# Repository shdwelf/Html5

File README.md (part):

# bip39-haiku-workbench

Offline workbench for mining **BIP-39 mnemonics that scan as 5-7-5 haiku**, deriving
their BIP-44 addresses, and moving data between tools through a **piped inbox**.

The application now combines both repository lineages. The canonical main canvas is
the complete uploaded **23 August Gen2 Webxdc/quine build**, with a surgical Poetry
validator repair applied before it executes rather than replacement look-alike
components. The small `⌘` switcher opens the maintained TypeScript recovery suite
and every other distinct, non-empty HTML application from the gen-2 patch.

```bash
npm install
npm run dev     # http://localhost:5173
npm test        # full test suite, including byte-identity locks for the uploads
npm run build   # dist/index.html + dist/bip39-haiku-workbench.xdc
```

The production build is inlined by `vite-plugin-singlefile`, so `dist/index.html`
runs standalone from the filesystem. `scripts/build-xdc.mjs` then packages that
same combined application, its icon, manifest, and static companion tools as a
Webxdc ZIP for ArcaneChat / Delta Chat.

## Combined codebases

| Switcher entry | Source | Integration rule |
| --- | --- | --- |
| **Gen2 · Aug 23** (default) | `bip39-haiku-workbench-gen2-2026-08-23T11-46-10-756Z.html` | Full uploaded 12-tool canvas plus strict Poetry syllable repair |
| **Gen2 · Aug 14** | `bip39-haiku-workbench-gen2-2026-08-14T20-01-22-058Z.html` | Exact earlier seven-tool generation |
| **Quip build** | `bip39-haiku-workbench-quip.html` | Exact mnemonic explorer bundle |
| **Classic wallet** | `bip39_haiku_wallet.html` | Exact standalone miner and encrypted wallet list |
| **Pattern validator** | `haikubip39.html` | Exact classic haiku/repeated-word validator |
| **Recovery suite** | `src/` | Maintained React/TypeScript tools described below |

The applications run in same-origin `iframe srcdoc` boundaries because every upload
is already a complete compiled document with its own React runtime, global CSS,
`#root`, storage, and download handlers. This is deliberate isolation, not a visual
port: `test/codebase-archive.test.tsx` pins the original SHA-256 of all five documents,
and `test/poetry-validation.test.ts` signature-locks the two targeted Gen2 repairs.
The old Poetry counter double-subtracted consonant-`le` endings, while its line builder
could abandon a target after drawing a word that did not fit. The repair shares the
validator pronunciation table, only selects words that fit the remainder, and accepts
exact form counts—never a third line of 4 or 6 for 5-7-5. The second 23 August upload
is omitted only because it has the same SHA-256 as the first; `bip39haiku.html` is
omitted because it is zero bytes.

## Provenance

This repository was empty apart from a README. The application source was recovered
from the archive repo [`shdwelf/Html5-sync-incoming`](https://github.com/shdwelf/Html5-sync-incoming):

| Piece | Recovered from |
| --- | --- |
| Workbench app (React + Vite + Tailwind, `src/lib/wallet.ts`, `src/lib/syllables.ts`, `src/lib/enso.ts`) | `build-bip-39-haiku-wallet.zip` |
| Piped inbox concept and UI | `hyper-portal-2.27.0-PIPED-installer.html` (inside `Internal storage.7z`) |
| Recovery Lab (missing-word brute force, typo/anagram repair, vanity mining) | `crypto-mnemonic-mining-app.zip` |
| Art Gallery catalog, greedy 5-7-5 fallback, syllable-exception cleanup | vanilla workbench in [`shdwelf/Html5`](https://github.com/shdwelf/Html5) (`js/haiku-catalog.js`, `js/syllables.js`) |
| Vault file format + standalone decryptor | `HAIKUv4/v5`/`DECRYPTORv1.html` lineage (`Haiku Supplies.zip`) and the vanilla workbench's WebCrypto vault |

The two never shipped together: the haiku workbench had no inbox, and the
hyper-portal build that had the inbox had no haiku tool. Wiring them together —
and repairing the inbox on the way — is what this repo does.

`scripts/wormhole-fetch.mjs` is a small utility kept from that recovery work:
given `WH_URL=<link>` it opens a wormhole.app drop in real chromium (via
playwright) and captures every file — the link is end-to-end encrypted in the
URL fragment, so only a real browser can decrypt it. It runs anywhere
playwright + chromium are installed (a laptop, a GitHub runner with the
workflow permission).

## Repository-wide Java / TiddlyWiki editions

The new [Repository Wiki build](tools/wiki-workspace/README.md) produces actual
ACME/TJWS-hosted `wiki.in.a.jar`, `more.wiki.in.a.jar`, and `tiddlywiki.in.a.jar`,
plus a native TiddlyWiki HTML/Webxdc edition and MediaWiki XML export. Each JAR
contains a per-file source catalog and a deduplicated exact-byte repository vault,
with private caches/credential paths explicitly excluded. The extended library
adds backlinks, bibliographic URLs, revision conflicts/history and Haiku-v1
compatible encrypted page/file exchange. These are **new repository editions**,
not a claim to have recovered historical More Wiki 0.9.9 or translated arbitrary
JavaScript into JavaCard. See the [source-checked research and limitations](docs/wiki-workspace-research-2026-10-15.md).

```sh
npm ci
npm run build:wiki-workspace           # JDK 11+, Python 3, tar, curl; outputs dist/wiki/
java -jar dist/wiki/more.wiki.in.a.jar 3003
npm run test:wiki-workspace
npm run test:wiki-server               # real executable-JAR HTTP + persistence tests
```

The classic wiki's Calendar now uses font-independent SVG navigation, an
always-visible month grid and an event-page form; no pre-existing events are
required. TiddlyWiki HTML/XDC carry previews and metadata; the complete eligible
binary vault lives in the JAR editions. Nothing is uploaded to a remote wiki.

## Standalone viewers

- **[HTML5 Offline Viewer](offline-viewer.html)** — curated public catalogue for the locally bundled Helios Observatory and Prime Viewer apps, plus the local WebXDC player. `python3 scripts/build-private-html5-offline-viewer.py` creates a separate ignored delivery ZIP from the same fixed app allowlist.
- **[HTML5 Offline Library for Android](apps/html5-offline-launcher/README.md)** — public and curated private APK build instructions. CI publishes only the public APK artifact; the two-app private APK is built and verified without public artifact upload.
- **[Wiki in a Jar](wikiinajar.html)** — the 2008 USB-stick personal wiki (`wiki.in.a.jar` 0.8) rebuilt as one offline HTML file and a Webxdc bundle: same `.wiki` page model, same `[[wiki:]]`/`[[img:]]`/`[[djvu:]]`/`[[tags:]]` namespaces, vCard contacts, DjVu reading via the vendored WASM decoder, and webxdc chat sync. Ships as `wikiinajar.xdc` (`npm run build:wikiinajar`) with the repository Markdown library (root deep dives + `docs/*.md`) converted to wiki pages in its Docs tab; see [the deep dive](wikiinajar-deep-dive.md), the seeded **Wiki in a Jar** documentation page inside the app, and the Java-side patch in [tools/wikiinajar/](tools/wikiinajar/).
- **[Keyspace Viewer](keyspace.html)** — BIP-39 geometry, measured statistical layers, wallet derivatives, and keyspace projections.
- **[Prime Viewer](prime.html)** — exact prime atlas, residue-class solar system, prime constellations, counting statistics, gaps, and integer inspection. See [PRIME.md](PRIME.md).
- **[Helios Observatory](astronomy.html)** — time-propagated solar orrery, curated celestial catalog, Earth-centered NEO radar, and modeled meteor streams. See [ASTRONOMY.md](ASTRONOMY.md).
- **[Flash Decompiler Timeline](flash-decompiler.html)** — Wayback/NATA2-style raw SWF retrieval, configurable CORS proxy triage, Behind The Dune version timeline, easter-egg notes, and a GitHub Actions path for JPEXS/FFDec decompilation without committing large NSFW binaries.
- **[Red October · 4D Command Theater](public/apps/red-october-command-viewer/)** — an offline story-index globe, selectable schematic silhouettes, story/time controls, VRML 2.0 and Xena XML export. The map markers are fictionalized narrative anchors, not real track data; the hull model has no precise internal layout. Ships as `red-october-command-viewer.xdc`; see [the viewer source/provenance research](docs/red-october-4dwm-research-2026-10-09.md) and [the Archive.org/Jane’s/Bulletin source audit](apps/red-october-command-viewer/data-sources/archive-research.md).
- **[Greeran Family Tree · 4DWM](greeran-family-4dwm.html)** — the Drive family-tree Webxdc with an offline spinning globe, playable 1774–2023 record timeline, Tree-of-Life preface, baseline GEDCOM export, and public-domain World English Bible EPUB. The first-name merge remains pending until an authorized Kirkpatrick ARJ and raw GEDCOM are available. See [the import/build notes](docs/greeran-family-4dwm.md) and [the ebook/data status](docs/greeran-family-tree-ebook-and-data-status.md).
- **[FOUR CORNERS 4Dwm](four-corners.html)** — the only place four US states meet: the surveyed quadripoint, Navajo volcanic field necks, the San Juan energy basin, the uranium legacy, and the ancestral Puebloan core, over a curated IDW relief that is honest about not being a DEM. See [docs/four-corners.md](docs/four-corners.md). Ships as `four-corners.xdc` and as the [TI calculator port](#four-corners-on-ti-calculators-four-corners-calc) below.
- **[SoCal Subsurface 4Dwm](socal-subsurface.html)** — an offline basin theater with terrain, geocache GPX import, radio/propagation and orbital views. Ships as `socal-subsurface.xdc`, plus the single-file [`socal-subsurface-inlined.html`](socal-subsurface-inlined.html) / `socal-subsurface-inlined.xdc` edition; the legacy download name `planet-viewer-4dwm.xdc` now carries this same canonical SoCal package and manifest.
- **[Greeran Subsurface 4Dwm](greeran-subsurface.html)** — the Greeran book's 2001 biography deep-dive (Glendora → West Covina → Goleta → Santa Barbara) rendered as a SOCAL-style subsurface theater. Ships as `greeran-subsurface.xdc`.
- **[Glendora High 4Dwm](glendora-high-4dwm.html)** — Class of 2001 at 1600 E Foothill Blvd, "now that I am a graduate". Ships as `glendora-high-4dwm.xdc`.
- **[ESGVROP 4Dwm](esgvrop-4dwm.html)** — East San Gabriel Valley ROP & Technical Center, the summer-2001 deep dive across the Del Norte and Sunflower campuses. Ships as `esgvrop-4dwm.xdc`.
- **[Dalton Race 4Dwm](dalton-race-4dwm.html)** — Big Dalton / Little Dalton terrain with pips, route pointers, and VRML export. Ships as `dalton-race-4dwm.xdc`.
- **[INGRESS INTEL 4Dwm](ingress-intel.html)** — an Ingress intel theater that actually tries to connect: a six-rung connection ladder (same-origin → your relay → public CORS proxy → pasted capture → webxdc peer → offline register) with a verdict and a fix printed per rung, the same intel payload drawn on a planet globe with geodesic links, spherical control fields and a live day/night terminator *and* on the SoCal basin plate, and an honest `SIM` watermark whenever nothing live answered. Decodes/encodes `getEntities`, portal-detail and plext payloads, IITC GeoJSON/KML/CSV exports and intel permalinks. Ships as `ingress-intel.xdc`. See [docs/ingress-intel-map-viewer.md](docs/ingress-intel-map-viewer.md) and the [connector research](docs/ingress-intel-connector-research-2026-10-07.md).
- **[CASEFILES · 4DWM](casefiles.html)** — the static-analysis lab for the 1998 kr0me corp Tripod library and the 1996 Rodger Ramrod DOS4GW package: Wayback CDX recovery behind a SHA-1 gate, fflate unzip in memory, SLEIGH x86 16/32, the Ghidra decompiler as WebAssembly — and a 4DWM plate that draws the capture corpus as a ridged relief over a playable capture-date timeline, and whatever artifact is on the table as a bit-plane relief with an offset sweep. Motif-style pips carry the record; VRML 2.0 exports the current field. Ships as `casefiles.xdc` (a real webxdc ZIP) and as the single-file `casefiles-inlined.html`; see [docs/casefiles-4dwm.md](docs/casefiles-4dwm.md).
- **[Lantronix Lab](lantronix-lab.html)** — the deep dive that starts at a thumb-sized Lantronix xPort Pro (16 MB flash, ColdFire, µClinux) and ends at a generated EAGLE design for a mains-powered RS-232 ↔ RJ45 wallplug: a device matrix that keeps DSTni-EX (x86) and DSTni-FX (ColdFire) apart, a client-side firmware triage tool that goes magic → container → architecture → Ghidra language, the µClinux stack Lantronix actually ships with a DistroWatch-reality-check on alternatives, a JVM-vs-Java-Card panel with a real `.class`/`.cap` reader and bytecode disassembler, and an EDA viewer that renders the generated `.sch`/`.brd` and re-runs the design rules in the browser. See [docs/lantronix-uclinux-deep-dive-2026-10-08.md](docs/lantronix-uclinux-deep-dive-2026-10-08.md) and [hardware/lantronix-wallplug/](hardware/lantronix-wallplug/).
- **Wallplug family** — the xPort Pro wallplug is now one of four generated, rule-checked EAGLE designs built by a single design-agnostic pipeline: a **WiMAX CPE** carrier for a PCI Express Mini Card 802.16e modem (Intel Centrino 6250; USB half wired, PCIe half honestly left open), a **Raspberry Pi Zero 2 W wall-socket** carrier with wired Ethernet (WIZnet WIZ850io on SPI0) and Ethernet-over-powerline (chargebyte PLC Stamp mini 2 on SPI1), and a standalone **HomePlug Green PHY ↔ Ethernet bridge** (QCA7005 + ESP32 + W5500). Every pad coordinate is imported from a published KiCad footprint by `tools/import-kicad-footprints.mjs`; creepage follows the chargebyte datasheet's 8 mm / 6.5 mm / 4000 Vac figures where that module is fitted; and `tools/replacement-parts.mjs` records 83 sourced substitutes with verdicts, including the ones marked *not-a-substitute*. See [docs/wimax-pi-powerline-variants-2026-10-08.md](docs/wimax-pi-powerline-variants-2026-10-08.md) and [hardware/](hardware/).
- **[CITY SUBSURFACE 4Dwm](lawrence-subsurface.html)** — the shared SoCal-family city engine ships as fifty-nine apps: Lawrence KS, Atlanta GA, Kansas City MO, Buffalo NY, Toronto ON, statewide California/Nevada/Arizona/Utah/Colorado/New Mexico/Oregon/Washington/Idaho/Montana/Wyoming/North Dakota/South Dakota/Nebraska/Kansas/Oklahoma/Texas/Iowa/Missouri/Minnesota/Louisiana/Mississippi/Alabama/Georgia/Wisconsin/Michigan/Illinois/Indiana/Ohio/Pennsylvania/Arkansas/Kentucky/Tennessee/Virginia/West Virginia/North Carolina/South Carolina/Florida/Maryland/Delaware/New Hampshire/Vermont/Maine/Massachusetts/Connecticut/Rhode Island/Alaska/New Jersey/New York/Hawaii frames, and Guam, American Samoa (Tutuila–Manuʻa), U.S. Virgin Islands and Midway territory frames. Each keeps the Gazetteer, local `rec.geocache` GPX import, BagIt export and plan view. Lawrence has a disclosed 8×8 USGS 3DEP sample grid plus five verified GNIS points; the state/territory starter registers use per-ID GNIS primary points with synthetic relief rather than claiming DEMs. Build with `npm run build:city-subsurface`; see [the evidence/build notes](docs/city-subsurface.md).
- **[COUNTRY VIEWER](country-viewer.html)** — the PC-Globe-style country viewer (S4 country thread): an offline, searchable full-coverage register of 233 countries/territories with CIA World Factbook notes, packaged as `country-viewer.xdc` — capital and reference-point coordinates, area, population, languages, government type, and national-anthem titles — pinned to `factbook/factbook.json@144d6977b2b0` with per-file SHA-256 in `resources/country-viewer/`. Build the dataset and bundle with `npm run build:country-viewer`. The 1990 PC Globe database itself is decoded by the dependency-free Java reader in `tools/pcglobe/` (dump in `research/pcglobe-java/`), and the [planet viewer](planet-viewer-4dwm.html) opens on a GLOBE plate that reuses the Red October globe with these capitals as markers.
- **[Historical Network Viewer — Keyhole slice](historical-network-viewer.html)** — the S6 evidence viewer for Denver's Keyhole BBS: dated observations, snapshot rights/capture status, a city-level place with no invented pin, merge/rejected-match logs, negative FidoNet searches, JSON/CSV export, and local TEXTFILES plus FTS-5000 FidoNet nodelist import with browser-side SHA-256. It is a citation fixture and local-import tool, not a bundled historical dataset; see [the fixture notes](docs/historical-network-keyhole-fixture-2026-10-22.md) and [FidoNet adapter notes](docs/historical-network-fidonet-adapter-2026-10-22.md).
- **[FOUR CORNERS · calculator port](four-corners-calc.html)** — the bench for the TI-83/89/92 port: it runs the port's own C core transpiled to an ES module, so the preview *is* the port.

Every 4Dwm-family Webxdc rebuilds from one command — `npm run build:4dwm`
chains the fourteen standalone packagers (casefiles, bluetops, cheyenne,
dalton-race, esgvrop, four-corners, glendora-high, greeran-family,
greeran-subsurface, ingress-intel, sanborn-restaurant, SoCal Subsurface (also
mirrored to the legacy `planet-viewer-4dwm.xdc` filename) and its inlined
edition, vincennes), then
builds the fifty-nine shared city/state/territory bundles; each app also has its own
`npm run build:<name>`, and `npm run check:casefiles` proves CASEFILES' two
derived artifacts still match their sources byte for byte.

## Tools

| Tab | Purpose |
| --- | --- |
| **Ensō Forge** | Parameterised ensō brushstroke; its packed *Ensō ID* doubles as the vault password. |
| **Haiku Wallet** | Mines 128-bit mnemonics until the 12 words partition into 5-7-5, derives `m/44'/0'/0'/0/0`, stores them in an AES-256 vault. |
| **Inspector** | Validates a phrase's BIP-39 checksum, shows its syllable/5-7-5 breakdown, derives address + xpub. |
| **Recovery Lab** | Brute-forces `?` words, repairs typos/anagrams, mines BTC vanity addresses — optionally pinned to an address fragment you know is yours. |
| **Art Gallery** | 100 curated checksum-valid BIP-39 art patterns (repeat stems, haiku/poetic scans), re-verified live on every render. |
| **MonKey Miner** | Mines Banano wallets for rare monKey accessories, fully offline. |
| **Autobiography** | Chapters plus an embedded filesystem; exports as one self-contained HTML book. |
| **Crypto Cookbook** | The 83-section reference, framed byte-identical from `/apps/cookbook/`. |
| Terminal / wAves / Market | Carried over from the original build. |

## Recovery Lab

Ported from the recovered `crypto-mnemonic-mining-app` (June 2026, ethers-based)
onto this repo's own stack — `@scure/bip39` for checksums, the wallet's BTC
P2PKH derivation instead of ethers/bananojs, no new heavy dependencies.

**Find `?` words.** Mark each unread word with `?`. A BIP-39 phrase carries its
own checksum, so of the 2048 words that could fill a slot only ~1 in 16
survives for a 12-word phrase (1 in 256 for 24 words) — the checksum does most
of the work. One missing slot scans instantly; two walks 2048² = 4.2M
combinations chunked and cancellably (a few minutes at most; more than two is
out of scope for a browser lab).

**Repair typos & anagrams.** Words outside the wordlist are replaced by their
anagrams (the wordlist has 56 anagram classes: `canoe/ocean`, `armed/dream`,
`alert/alter/later`…) and near edits — Levenshtein distance ≤ 2. If every word
is valid but the checksum still fails, each single word is tried against its
edit-distance-≤ 1 neighbours plus anagram mates, catching the silent swap that
spell-check cannot see.

**Pinning to an address.** Repairs and fills frequently have *several*
checksum-valid outcomes — the checksum cannot tell them apart. Paste the first
characters of an address you know the wallet owned and only candidates whose
BTC legacy derivation contains that fragment survive. That is also what makes
recovery deterministic instead of "first 20 valid hits".

**Vanity mining.** Mines fresh 12-word mnemonics until the BTC legacy address
starts with your prefix (case-sensitive Base58; the leading `1` is optional).
Each extra character is ~58× the work: two characters are seconds, three are
minutes, four are a long night. Cancels like everything else.

## Art Gallery

The 100-entry catalog shipped with the vanilla workbench port
(`js/haiku-catalog.js` in `shdwelf/Html5`): 40 eleven-word repeat stems with
their checksum word, 20 fifteen-word, 10 twenty-four-word patterns, and 30
haiku/poetic scans. In BIP-39 the last word is never free — its low bits are
the checksum of everything before it — so an eleven-word stem of one repeated
word pins exactly one valid ending. The stem is chosen; the checksum decides
the last word. These are found art.

Every card re-validates its phrase against the real BIP-39 checksum on render
(and `test/catalog.test.ts` locks all 100), so a corrupted import is visible
immediately. Haiku entries display their greedy 5-7-5 layout with per-line
syllable counts, and any entry can be piped to the Inspector.

## Inspector upgrades

- **Per-word chips** under the input — each word with its syllable count,
  red when not in the wordlist (ported from the mining app's live validation).
- **Explorer section** (Coleman-style): BIP-39 passphrase ("25th word"),
  custom derivation path, seed hex, root xpub, and a first-N accounts table.
  Private keys stay hidden behind a per-row reveal; the root xprv is never
  rendered. A passphrase changing every derived address is demonstrated in
  `test/syllables-explorer.test.ts`.
- **Greedy 5-7-5 fallback** now lives in `src/lib/syllables.ts`
  (`greedy575`), shared by the Inspector and by `itemFromMnemonic`, replacing
  the old behaviour of dumping a non-haiku phrase onto a single line. The
  ported version had a defect: words after the third line filled were
  silently dropped. Fixed here — the layout always accounts for every word —
  and locked by test.
- The syllable **exception table** dropped three dead keys (`area51`,
  `create_`, `science_`) that could never match after non-letters are
  stripped.

## Vault files and the standalone decryptor

Besides the existing crypto-js exports, the wallet now speaks a
format-designed-for-archival vault file:

```
haiku-vault-v1.<base64( 0x01 | salt(16) | iv(12) | ciphertext‖tag )>
```

AES-256-GCM, PBKDF2-HMAC-SHA256 × 120,000, salt separate from the IV so one
Ensō ID can safely back multiple files. Implemented with `@noble/ciphers` in
the app; round-trip, wrong-password and single-character-tamper cases are
covered by `test/vaultfile.test.ts`.

**🧰 Standalone decryptor ⬇** generates a single self-contained HTML page
(no imports, no network, verified by test) that decrypts `.haikuvault` files
with native WebCrypto — optionally with the current vault pre-embedded. Save
it next to your backups: it opens from a USB stick in fifty years' time, which
is the whole point of an offline vault. **📥 Import .haikuvault** decrypts
with the current Ensō ID and merges without duplicates.

## The piped inbox

Any tool can **park** a value in the inbox (`📤 Pipe`) or **pull** one out
(`📥 Pull from Pipe`). The floating inbox can also **push** a value straight into
a tool, which focuses that tab and delivers the payload.

Content is typed (`mnemonic`, `haiku`, `address`, `xpub`, `json`, `text`) and the
UI only offers targets that accept the type — so a mnemonic mined in the wallet
can be sent to the Inspector, but an address cannot.

### What was broken

The original provider (`hyper-portal-2.27.0-PIPED-installer.html`) kept a single
`inboundPayload` slot and no persistence. Four concrete defects, each now covered
by a regression test in `src/pipe/PipeProvider.test.tsx`:

1. **Back-to-back sends lost data.** Delivery was one `useState` slot, so
   `sendToTool(a); sendToTool(b)` overwrote `a` before any consumer ran — only
   `b` arrived. Deliveries are now an append-only queue drained per tool.

2. **The inbox did not survive a reload.** Pipes lived only in React state, which
   makes "park this for later" meaningless across a refresh. Pipes and in-flight
   deliveries now persist to `localStorage`, with corrupt/quota-limited storage
   degrading to memory instead of throwing.

3. **Empty content read back as a miss.** `consumePipe` ended in
   `?.content || null`, so an empty string — legitimate payload — was
   indistinguishable from a missing pipe. Now `?? null`.

4. **Colliding ids.** Ids came from `Math.random().toString(36).substring(2,10)`.
   Since rows are keyed by id and `removePipe` filters on it, a collision deletes
   the wrong entry. Now `crypto.randomUUID()` with a timestamped fallback.

Additionally, consumption used to be an impure read (`consumeInbound` returned the
payload *and* cleared it), which is fragile under React StrictMode's double-invoked
effects. Delivery is now explicit: `usePipeReceiver` hands the payload to a handler,
records the delivery id in a ref, and acks it — so a repeated effect run cannot
apply the same payload twice.

I verified 1, 3 and 4 by running the new tests against a faithful replica of the
original provider and watching them fail. Defect 2 is likewise reproduced. The
late-mount guarantee (a delivery waits for a tool that has not been opened yet) is
hardening rather than a reproduced regression — the old code happened to survive
that case.

### Using it in a tool

```tsx
// produce
<PipeOutButton draft={{
  content: item.mnemonic, contentType: "mnemonic",
  sourceId: "wallet", sourceName: "Haiku Wallet", label: `${item.id} mnemonic`,
}} />

// consume: pushed deliveries
usePipeReceiver("inspector", (delivery) => setText(delivery.content));

// consume: user-initiated pull
<PipeInButton accepts={["mnemonic", "text"]} onReceive={(content) => setText(content)} />
```

## Recovered HTML5 apps (`/apps/`)

`npm run dev` also serves the other apps recovered from `Html5-sync-incoming`,
over the dev server's origin rather than `file://`:

| URL | App |
| --- | --- |
| `/apps/` | Index, with a live secure-context / microphone check |
| `/apps/anc-studio/` | ANC Studio Ultra — adaptive multi-band FxLMS over AudioWorklet |
| `/apps/cyberchef/` | CyberChef Renovated Kitchen — 519 recipes after unioning the Html5 and Html5-sync-incoming recipe sets, plus file input and save. Includes QR/Aztec generation and image decoding, CueCat and postal barcode recipes, Avery LabelPro-style N-up labels, an educational multiplicative ElGamal demonstration (not FHE), and offline SFX support. See the [barcode notes](docs/cyberchef-aztec-cuecat.md), [SFX coverage audit](docs/cyberchef-sfx-coverage-audit-2026-10-13.md), [field-cipher deep dive](docs/field-cipher-deep-dive-2026-10-14.md), and [recipe-sourcing notes](docs/recipe-sourcing-round-4-2026-10-14.md) and [round 5](docs/recipe-sourcing-round-5-2026-10-14.md) for the tested cryptography and historical recipes. |
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
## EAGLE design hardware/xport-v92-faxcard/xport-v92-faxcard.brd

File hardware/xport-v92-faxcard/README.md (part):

# xPort Pro V.92 Fax Card — telnet BBS + Group 3 fax in an HP EIO slot

Generated CAD. Do not edit these files: they are emitted by
`tools/build-wallplug-eagle.mjs --design=xport-v92-faxcard` from
`tools/xport-v92-faxcard-model.mjs`, and `--check` re-derives them and compares.

| file | what it is |
| --- | --- |
| `xport-v92-faxcard.lbr` | 18 packages, 15 symbols, 18 devicesets |
| `xport-v92-faxcard.sch` | 1 sheet, 27 instances, 23 nets |
| `xport-v92-faxcard.brd` | 150 × 100 mm, 2 layers, 32 elements, 115 pads — **unrouted on purpose** |
| `BOM.md` | every reference, its package, fit/DNP, zone and note |

## What it does

A card in the HP Enhanced I/O (EIO) expansion-slot form factor that puts a
Lantronix xPort Pro device server and a V.92 56k data/fax modem inside a
printer, bridged by an STM32 Nucleo-64:

```
PSTN ── RJ11 (J3) ── V.92 modem (U3) ── USART1 ── Nucleo-64 (J2) ── USART2 ── xPort Pro (X1) ── RJ45 ── Ethernet
        tip/ring      DAA + Class 1     PA9/PA10                   PA2/PA3                  telnet BBS
```

The xPort Pro's RJ45 and the modem's RJ11 both come out on the EIO faceplate.
The xPort Pro runs the telnet BBS front end; the modem answers and sends Group 3
fax; the Nucleo bridges the two serial links and drives the T.30 session.

## The EIO constraint, and what it forced

EIO uses the **3.3 V signalling of the conventional PCI bus**, will not accept
LIO cards, and is not mechanically interchangeable with MIO. Two consequences:

* **An STM32 cannot enumerate as a PCI target.** Reaching the printer's
  formatter through the slot needs a PCI-to-local-bus bridge. This revision does
  not have one.
* **HP does not publish the EIO pinout.** No finger is energised on a guess.

So `J5` is a 68 × 12 mm **mechanical keep-out carrying no copper**, and the card
takes power from `J1`, a 12 V tap. The card uses the slot for mounting and
faceplate registration and is otherwise electrically independent of the printer.
When the pinout is traced from a donor JetDirect card, `J5` becomes a real
PCI-32 3.3 V finger pattern.

**A Nucleo cannot physically live in the slot** — it is 70 × 70 mm with 8.5 mm of
header above the board. This is a development carrier; a production revision
would put the same MCU down as a bare LQFP.

## Host wiring

| Nucleo-64 | MCU | other side | note |
| --- | --- | --- | --- |
| D1 | PA2 | X1 pin 5 `DIN` | USART2_TX → xPort Pro, via R8 100 Ω |
| D0 | PA3 | X1 pin 4 `DOUT` | USART2_RX ← xPort Pro, via R7 100 Ω |
| D8 | PA9 | U3 `RXD` | USART1_TX → modem, via R4 100 Ω |
| D2 | PA10 | U3 `TXD` | USART1_RX ← modem, via R3 100 Ω |
| D9 | PC7 | U3 `!DCD` | carrier detect |
| D10 | PB6 | U3 `!DTR` | |
| D11 | PA7 | U3 `!RI` | ring indicator |
| VIN | — | 12 V | UM1724 specifies 7–12 V |

**The trap:** on a Nucleo-64, PA2/PA3 are also the ST-LINK virtual COM port
(MB1136 SB62/SB63 ON, SB13/SB14 OFF). Leave the bridges closed and you get a
free USB console, but the ST-LINK shares the xPort Pro link. Open SB62/SB63 for
a production card, or swap the two links.

Both links are 3.3 V TTL end to end — the xPort Pro serial channel and the modem
module are both 3.3 V parts — so there is **no level shifter**. The 100 Ω
resistors are hot-plug and fault limiting, not translation.

No hardware flow control: 115200 8N1 against a 14.4 kbps fax channel leaves 8×
headroom for an interrupt-driven RX. `!RTS`/`!CTS` are in `UNCONNECTED`.

## Design rules

| rule | value | where it comes from |
| --- | --- | --- |
| working clearance | 1.0 mm | SELV only: 12 V in, 3.3 V derived, IPC-2221 B1 for ≤ 30 V |
| minimum pad-to-pad | 0.35 mm | `--check` geometry rule |
| mounting hole ↔ copper | 3.2 mm | `--check` |
| PSTN isolation | 3 kV class | inside the modem module; the board must not undo it |
| board | 150 × 100 mm, 2 layers, 1.57 mm FR-4 | PCI-class card thickness; inside a half-length PCI envelope |

There is no mains zone, so `--check` reports the worst mains↔SELV creepage as
`Infinity` — that is correct here, not a gap in the check.

## Power budget (datasheet maxima, not typicals)

| rail | source | loads | margin |
| --- | --- | --- | --- |
| 12 V | J1 tap, sized 6 W | U1 buck input ≈ 154 mA + Nucleo via VIN ≈ 250 mA = 404 mA | 19 % |
| 3.3 V | LM2576S-3.3, 3 A | xPort Pro 300 mA + modem 100 mA + LEDs 30 mA = 430 mA | 86 % |

`VIN` on the Nucleo power header is specified 7–12 V, which is why the card runs
12 V rather than back-powering the header's 3V3 pin. That pin is deliberately
open and listed in `UNCONNECTED`.

**Known refit before building:** `L1` is the shared block default 100 µH. The
LM2576 nomogram wants more inductance at 12 V in than at 5 V in — re-read the
L-vs-VIN chart and refit. This is on the schematic too.

## The modem

The pinout follows the **Radicom V92HM4-RC** class of part: controller-based, no
external memory, 3.3 V VCC with 5 V tolerant I/O, serial TTL DTE, 3 kV isolation,
V.92 data to 56 kbps, **14.4 kbps fax**, V.253 voice, DTMF, about 1 × 1 × 0.3 in
at 66–78 mA and 270 mW. Multi-Tech's SocketModem is the through-hole alternative
and is specified to connect straight to a UART at up to 230.4 kbps.

**Module pinouts are not standardised.** Confirm the pin order against whichever
module is actually bought before releasing the board.

## Fax protocol

Class 1 is **TIA/EIA-578**; Class 1.0 is **T.31**. The modem handles the
V.21/V.17/V.29/V.27ter modulation; the host drives the T.30 session with
`+FCLASS=1`, `+FRH`, `+FTH`, `+FTM`, `+FRM`, `+FTS`, `+FRS`. Group 3 tops out at
14.4 kbps. `+FAA=1` gives adaptive answer — answer as fax or fall back to data
on the same call, which is what a printer sharing one line wants.

Three details the firmware in `firmware/xport-v92/` encodes because they are
easy to get wrong:

* **The DCE generates the FCS on transmit.** The host sends address + control +
  information only on `+FTH`. On `+FRH` the DCE hands back the frame *including*
  its two FCS octets, so the host verifies on receive and never computes on send.
* **The P/F bit decides whether the call stays up.** Bit 4 of the control octet:
  clear, and the modem answers `CONNECT` and keeps transmitting flags; set, and
  it answers `OK` and drops carrier. That is how TSI and DCS go out in one
  `+FTH` burst — first frame P/F=0, last frame P/F=1.
* **DLE is a second escape layer, not part of HDLC.** `10 10` is one literal
  DLE, `10 1A` is two, `10 03` ends the frame, `10 04` aborts. A 0x10 in a page
  image that is not escaped reads as a control command.

## Bring-up

1. Power from a fused 12 V tap at J1. Check 3.3 V at TP4. The LM2576's ON/OFF is
   tied to GND (always on) and FB is internally bonded on the fixed-output part.
2. Flash the Nucleo over its own USB before fitting, or in place with the ST-LINK
   if SB62/SB63 are still closed.
3. Set the xPort Pro up on its own port: it defaults to 9600 8N1 and boots with
   a setup banner. Give it a static IP or a DHCP reservation, then point the BBS
   front end at port 23.
4. Probe the modem at TP5 (`TXD`) and TP6 (`RXD`) before trusting the bridge:
   `AT` → `OK`, then `AT+FCLASS=?` to confirm Class 1 is available.
5. Only then test against the PSTN — and only with a modem approved for the
   local line.

## Safety

* No mains on this card. Everything is SELV.
* The PSTN is **not** SELV. The isolation is inside the modem module; `TIP` and
  `RING` run only between U3 and J3, with no test point on that pair, because a
  test point there would defeat it.
* Connecting equipment to a telephone line is regulated in most countries. A
  modem not approved for the local PSTN cannot lawfully be connected to it
  whatever this board does.
* The 12 V tap must be fused at the source. This card has a ferrite on the entry,
  not a fuse.
* The EIO pinout is unpublished. Do not energise a finger on a guess, and do not
  assume a JetDirect pinout carries over to another EIO accessory.

## Footprint provenance

| package | source |
| --- | --- |
| `XPORTPRO` | shared with the xPort Wallplug design — Lantronix xPort Pro Integration Guide 900-557 rev K table 2-2, plus `tridrao/SparkFun-KiCad-Libraries` `XPORT.kicad_mod` |
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
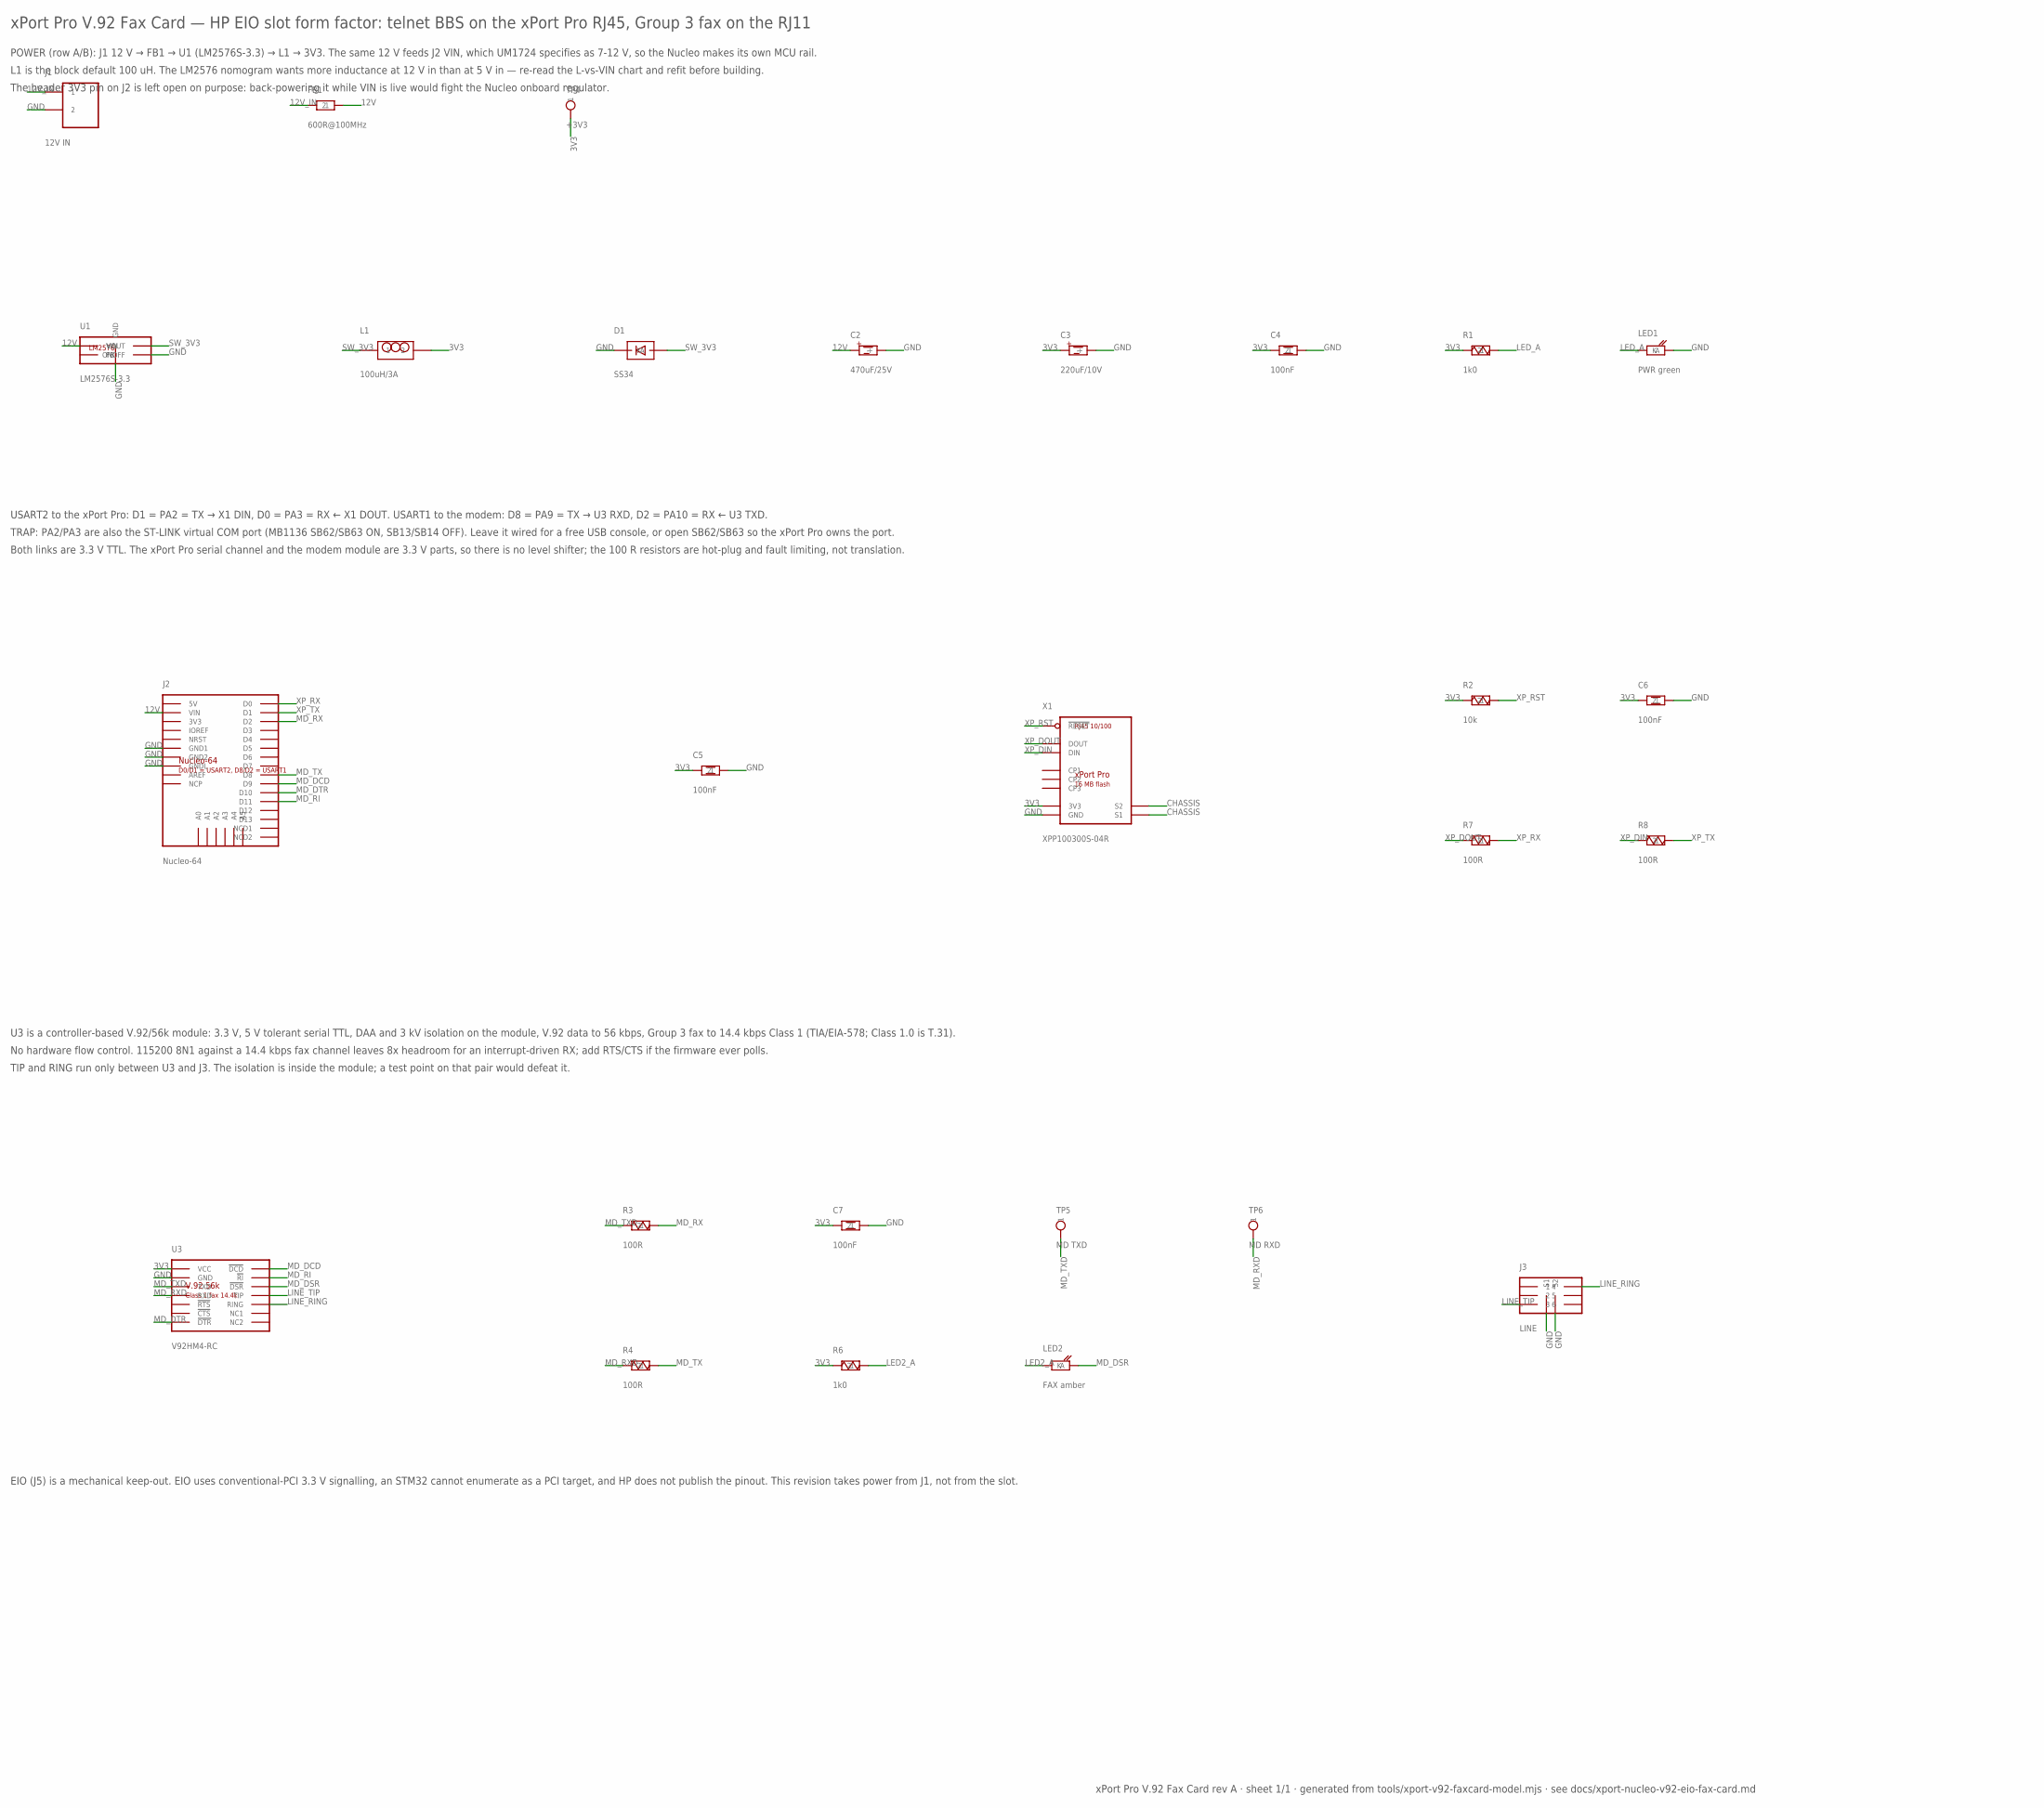
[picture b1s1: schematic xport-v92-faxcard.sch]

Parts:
C2: 470uF/25V; CP-D10-P5
C3: 220uF/10V; CP-D10-P5
C4, C5, C6, C7: 100nF; C0603
D1: SS34; DO41
FB1: 600R@100MHz; FB-7.62
J1: 12V IN; TERM2-5.08
J2: Nucleo-64; NUCLEO64
J3: LINE; RJ11-6P4C
L1: 100uH/3A; LRAD12
LED1: PWR green; LED-5MM
LED2: FAX amber; LED-5MM
R1, R6: 1k0; R-7.62
R2: 10k; R-7.62
R3, R4, R7, R8: 100R; R-7.62
TP4: +3V3; TP
TP5: MD TXD; TP
TP6: MD RXD; TP
U1: LM2576S-3.3; LM2576S
U3: V92HM4-RC; V92MOD
X1: XPP100300S-04R; XPORTPRO

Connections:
3V3: C3.+, C4.1, C5.1, C6.1, C7.1, L1.2, R1.1, R2.1, R6.1, TP4.1, U3.VCC, X1.2 (3V3)
12V: C2.+, FB1.2, J2.VIN, U1.1 (VIN)
12V_IN: FB1.1, J1.1
CHASSIS: X1.S1, X1.S2
GND: C2.-, C3.-, C4.2, C5.2, C6.2, C7.2, D1.A, J1.2, J2.GND1, J2.GND2, J2.GNDL, J3.S1, J3.S2, LED1.2 (K), U1.3 (GND), U1.3_2 (GND), U1.5 (ONOFF), U1.P7 (GND), U1.P8 (GND), U1.P9 (GND), U1.P10 (GND), U3.GND, X1.1 (GND)
LED2_A: LED2.1 (A), R6.2
LED_A: LED1.1 (A), R1.2
LINE_RING: J3.4, U3.RING
LINE_TIP: J3.3, U3.TIP
MD_DCD: J2.D9, U3.!DCD
MD_DSR: LED2.2 (K), U3.!DSR
MD_DTR: J2.D10, U3.!DTR
MD_RI: J2.D11, U3.!RI
MD_RX: J2.D2, R3.2
MD_RXD: R4.1, TP6.1, U3.RXD
MD_TX: J2.D8, R4.2
MD_TXD: R3.1, TP5.1, U3.TXD
SW_3V3: D1.K, L1.1, U1.2 (VOUT)
XP_DIN: R8.1, X1.5 (DIN)
XP_DOUT: R7.1, X1.4 (DOUT)
XP_RST: R2.2, X1.3 (!RESET)
XP_RX: J2.D0, R7.2
XP_TX: J2.D1, R8.2

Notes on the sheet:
xPort Pro V.92 Fax Card — HP EIO slot form factor: telnet BBS on the xPort Pro RJ45, Group 3 fax on the RJ11
POWER (row A/B): J1 12 V → FB1 → U1 (LM2576S-3.3) → L1 → 3V3. The same 12 V feeds J2 VIN, which UM1724 specifies as 7-12 V, so the Nucleo makes its own MCU rail.
L1 is the block default 100 uH. The LM2576 nomogram wants more inductance at 12 V in than at 5 V in — re-read the L-vs-VIN chart and refit before building.
The header 3V3 pin on J2 is left open on purpose: back-powering it while VIN is live would fight the Nucleo onboard regulator.
USART2 to the xPort Pro: D1 = PA2 = TX → X1 DIN, D0 = PA3 = RX ← X1 DOUT. USART1 to the modem: D8 = PA9 = TX → U3 RXD, D2 = PA10 = RX ← U3 TXD.
TRAP: PA2/PA3 are also the ST-LINK virtual COM port (MB1136 SB62/SB63 ON, SB13/SB14 OFF). Leave it wired for a free USB console, or open SB62/SB63 so the xPort Pro owns the port.
Both links are 3.3 V TTL. The xPort Pro serial channel and the modem module are 3.3 V parts, so there is no level shifter; the 100 R resistors are hot-plug and fault limiting, not translation.
U3 is a controller-based V.92/56k module: 3.3 V, 5 V tolerant serial TTL, DAA and 3 kV isolation on the module, V.92 data to 56 kbps, Group 3 fax to 14.4 kbps Class 1 (TIA/EIA-578; Class 1.0 is T.31).
No hardware flow control. 115200 8N1 against a 14.4 kbps fax channel leaves 8x headroom for an interrupt-driven RX; add RTS/CTS if the firmware ever polls.
TIP and RING run only between U3 and J3. The isolation is inside the module; a test point on that pair would defeat it.
EIO (J5) is a mechanical keep-out. EIO uses conventional-PCI 3.3 V signalling, an STM32 cannot enumerate as a PCI target, and HP does not publish the pinout. This revision takes power from J1, not from the slot.
xPort Pro V.92 Fax Card rev A · sheet 1/1 · generated from tools/xport-v92-faxcard-model.mjs · see docs/xport-nucleo-v92-eio-fax-card.md

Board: 2 copper layers, 32 parts (0 on the bottom side), 23 nets, no tracks yet.

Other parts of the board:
H1, H2, H3, H4: MOUNT-M3
J5: EIO; EIO-EDGE

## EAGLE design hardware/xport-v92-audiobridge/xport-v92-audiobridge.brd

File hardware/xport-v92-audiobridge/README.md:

# POTS Audio Bridge — `xport-v92-audiobridge`

Telephone line on one side, a sound card microphone input and an agent headset on
the other. Second sheet of the xPort Pro V.92 card family; pairs with
[`../xport-v92-faxcard/`](../xport-v92-faxcard/), which does the fax and data
side of the same line.

Generated from [`tools/xport-v92-audiobridge-model.mjs`](../../tools/xport-v92-audiobridge-model.mjs)
by `tools/build-wallplug-eagle.mjs`, and verified by that tool's `--check`:
XML well-formed, every pin reference resolves, the emitted connectivity matches
the model's net table, and the geometry DRC passes.

## Signal chain

```
PSTN tip/ring
  └─ F1 50 mA ─ R1 100R ─┬─ RV1 275V ─┬─ C1 100nF ─┐   (surge + snubber)
                         └────────────┴────────────┴─ K1 hook relay
                                                        └─ T1 600:600 "wet"
                                                             ├─ centre-tapped hybrid
                                                             │    (620R x2 + RV2 470R trim)
                                                             ├─ 40 dB pad ──────────► J2 MIC IN
                                                             ├─ 15 dB pad ◄────────── J3 CARD OUT
                                                             └─ headset ────────────► J4 HEADSET
```

## Why each part is there

**The transformer has to be the "wet" type.** A wet 600:600 transformer is
specified to carry the 20–50 mA of DC loop current without saturating; a dry
voice transformer of the same impedance will work on the bench and go quiet or
distort the moment the line goes off-hook. Typical wet transformer DC resistance
is 40–150 Ω and inductance a few henries — that inductance is also what sets the
low-frequency response.

**The hybrid converts 2-wire to 4-wire.** The line is one pair; a sound card has
separate send and receive. Without the hybrid the agent hears their own voice a
beat late. This one is the resistive Wheatstone bridge of four 620 Ω arms, one
arm being the line itself in series with a DC blocking capacitor, nulled by the
470 Ω trimmer. The trimmer is not optional: a real line is not 600 Ω, and a
fixed resistor never nulls properly. Adjust for minimum sidetone with a real line
connected.

**The DC loop budget decides whether the exchange acknowledges the off-hook:**

| element | resistance |
| --- | --- |
| R1 surge limiter, tip | 100 Ω |
| R2 surge limiter, ring | 100 Ω |
| K1 relay contact | ~0.1 Ω |
| T1 primary DC resistance | 40–150 Ω |
| **total** | **240–350 Ω** (limit: 400 Ω) |

**The pads are sized from the actual levels**, not copied from a diagram:

- POTS nominal is −9 dBm, 275 mV rms into 600 Ω, 300–3400 Hz.
- A sound card line output is about 1 V rms; its microphone input is about 10 mV
  and supplies a ~5 V bias.
- Line → mic: R8 10 k series + R9 100 Ω shunt = **40 dB**, the conventional pad
  for this interface. R10 2.2 k keeps the card's bias current out of the
  transformer.
- Card → line: R13 470 Ω + R14 100 Ω = **15 dB**, deliberately heavier than the
  ~11 dB the levels need. Better to run the line slightly quiet than to
  overdrive the far end.

## Safety

The left of the board is line-referenced. 48 V DC sits on the pair, ring peaks
above 150 V, and a lightning or power-cross event puts far more on it.

T1 is the **only** isolation barrier between that and the PC. If you replace it
with anything not rated for the line, the sound card and the PC chassis become
part of the telephone circuit.

Isolation resistance from the line side to any touchable metal has to hold
**5 MΩ measured at 100 V DC**. Measure it after assembly.

The 3 mm creepage between the line side and the SELV side is enforced by
`tools/wallplug-drc.mjs` — `BOARD.zones.mains` and `creepageMm: 3.0` — and
T1's primary pins are individually marked line-referenced through
`PARTS[].padZones`, so the checker measures the transformer's own pin spacing
rather than trusting its silk outline. As built, the worst pair is
**T1.1 ↔ T1.6 at 3.28 mm**.

## Regulatory — read before connecting to a public network

**This is not a certified Direct Access Arrangement and is not approved for
connection to a public network.** Connecting terminal equipment to the PSTN is
regulated — FCC Part 68 in the United States, equivalent national approvals
elsewhere — and compliance is what a DAA is for: an approved module providing
the hook switch, the isolation and the impedance. Xecom, Cermetek and Siemens
all make them.

Two ways to stay legal:

1. **Put an approved DAA in front of this board.** Connect the hybrid behind the
   DAA rather than to the line directly.
2. **Keep this board on the private side of the network** — behind a PBX, or on
   a bench line — where no approval applies.

A third option worth considering: the V.92 module in the companion card already
has an approved DAA with 3 kV isolation, so take audio from *its* pins instead
of from the line. Whether the specific module exposes mic/speaker pins is not
something this repository has verified — check the datasheet before committing
to that route.

## Files

| file | what |
| --- | --- |
| `xport-v92-audiobridge.lbr` | 14 packages, 14 symbols, 15 devicesets |
| `xport-v92-audiobridge.sch` | 39 instances on a 520 × 420 sheet |
| `xport-v92-audiobridge.brd` | 88 pads, 43 elements, 29 nets, 120 × 90 mm |
| `BOM.md` | generated bill of materials |

Rebuild with `npm run build:xport-v92-audiobridge`, or check without writing
using `node tools/build-wallplug-eagle.mjs --check --design xport-v92-audiobridge`.

## What is not done

- **No layout routing.** The emitter places parts and verifies clearance; it
  does not route copper. `POUR` and the barrier are declared, traces are not.
- **Not measured.** No prototype, no return-loss measurement against the 10 dB
  requirement, no THD or frequency-response numbers. The hybrid balance in
  particular has to be trimmed against a real line.
- **Component values are computed, not validated.** The pad ratios follow from
  the published POTS and sound-card levels, but no scope trace confirms them.
- **The headset path is passive.** It will drive a headset from the hybrid; it
  will not drive a speaker. An agent needing hands-free volume wants an
  amplifier stage that is not on this board.

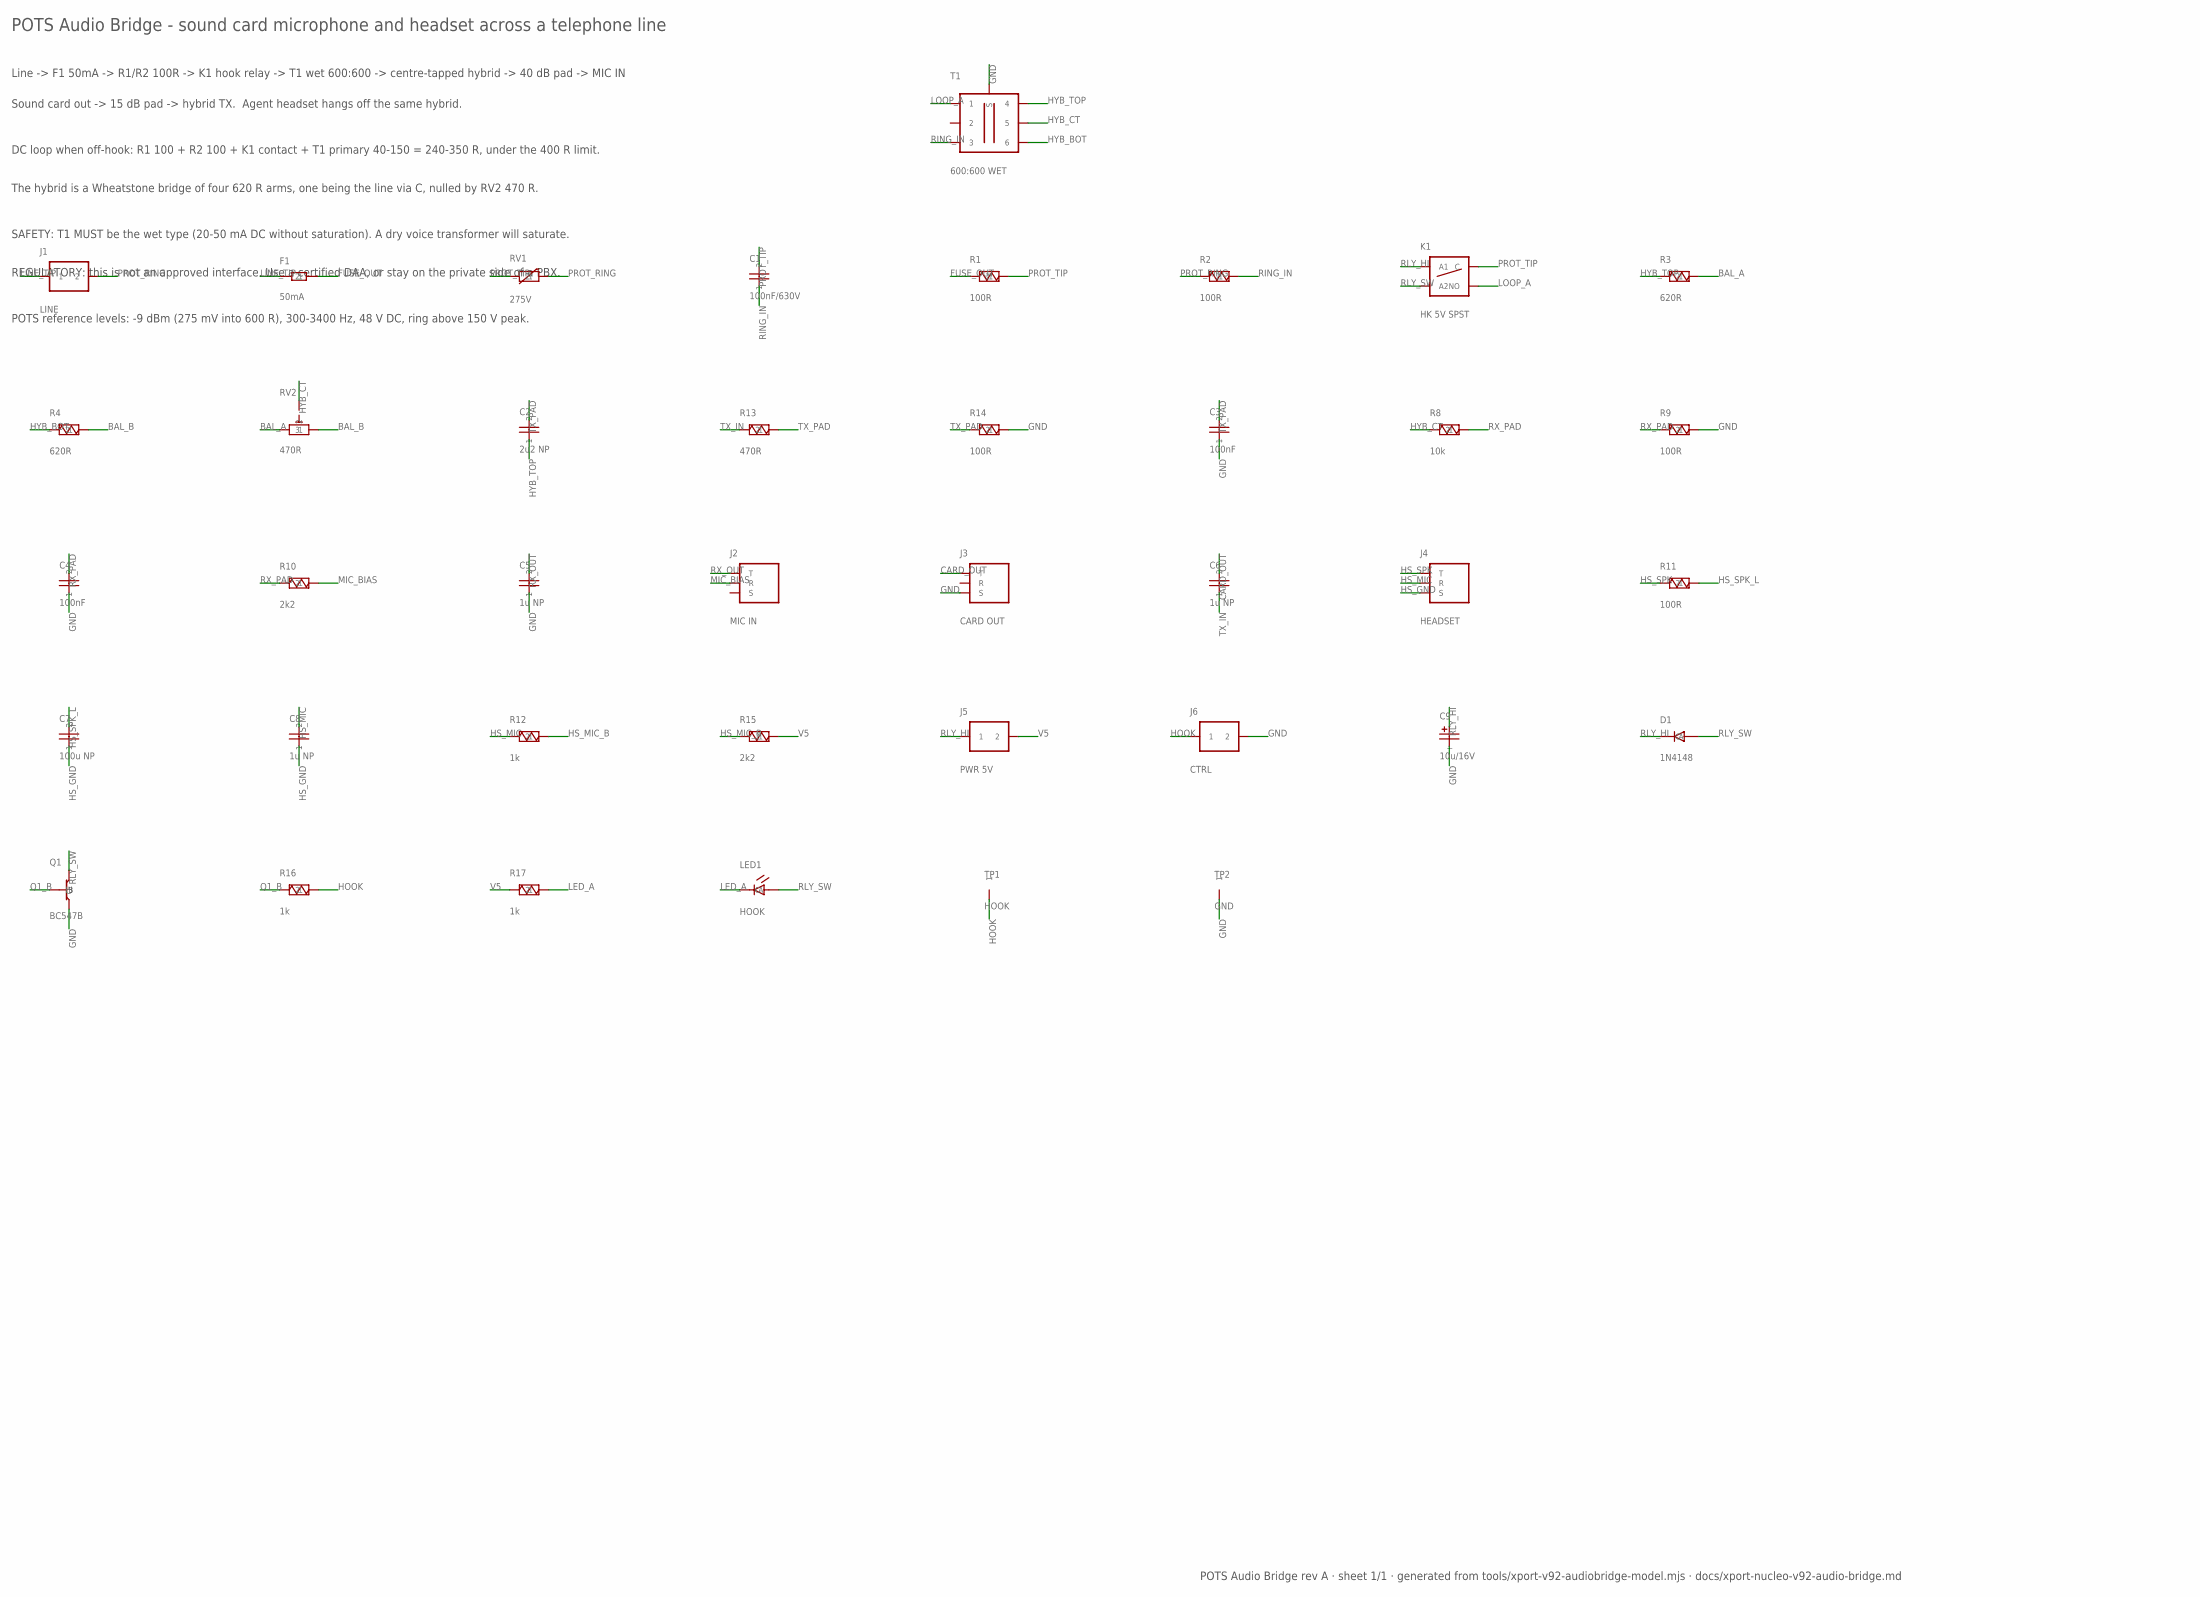
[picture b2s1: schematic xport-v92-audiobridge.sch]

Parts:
C1: 100nF/630V; C-5.08
C2: 2u2 NP; C-5.08
C3, C4: 100nF; C-5.08
C5, C6, C8: 1u NP; C-5.08
C7: 100u NP; C-5.08
C9: 10u/16V; CP-D8-P3.5
D1: 1N4148; DO41
F1: 50mA; R-7.62
J1: LINE; TERM2-5.08
J2: MIC IN; JACK-3P5
J3: CARD OUT; JACK-3P5
J4: HEADSET; JACK-3P5
J5: PWR 5V; TERM2-5.08
J6: CTRL; TERM2-5.08
K1: HK 5V SPST; RELAY-SPST
LED1: HOOK; LED-5MM
Q1: BC547B; TO92
R1, R2, R9, R11, R14: 100R; R-7.62
R3, R4: 620R; R-7.62
R8: 10k; R-7.62
R10, R15: 2k2; R-7.62
R12, R16, R17: 1k; R-7.62
R13: 470R; R-7.62
RV1: 275V; MOV-7.62
RV2: 470R; TRIM-3P
T1: 600:600 WET; XFMR-600
TP1: HOOK; TP
TP2: GND; TP

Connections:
BAL_A: R3.2, RV2.1
BAL_B: R4.2, RV2.3
CARD_OUT: C6.1, J3.1 (T)
FUSE_OUT: F1.2, R1.1
GND: C3.2, C4.2, C5.2, C9.2 (-), J3.3 (S), J6.2, Q1.3 (E), R9.2, R14.2, T1.S, TP2.1
HOOK: J6.1, R16.2, TP1.1
HS_GND: C7.2, C8.2, J4.3 (S)
HS_MIC: C8.1, J4.2 (R), R12.1
HS_MIC_B: R12.2, R15.1
HS_SPK: J4.1 (T), R11.1
HS_SPK_L: C7.1, R11.2
HYB_BOT: R4.1, T1.6
HYB_CT: R8.1, RV2.2, T1.5
HYB_TOP: C2.2, R3.1, T1.4
LED_A: LED1.1 (A), R17.2
LINE_TIP: F1.1, J1.1
LOOP_A: K1.4 (NO), T1.1
MIC_BIAS: J2.2 (R), R10.2
PROT_RING: J1.2, R2.1, RV1.2
PROT_TIP: C1.1, K1.3 (C), R1.2, RV1.1
Q1_B: Q1.1 (B), R16.1
RING_IN: C1.2, R2.2, T1.3
RLY_HI: C9.1 (+), D1.1 (A), J5.1, K1.1 (A1)
RLY_SW: D1.2 (C), K1.2 (A2), LED1.2 (C), Q1.2 (C)
RX_OUT: C5.1, J2.1 (T)
RX_PAD: C4.1, R8.2, R9.1, R10.1
TX_IN: C6.2, R13.1
TX_PAD: C2.1, C3.1, R13.2, R14.1
V5: J5.2, R15.2, R17.1

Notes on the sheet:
POTS Audio Bridge - sound card microphone and headset across a telephone line
Line -> F1 50mA -> R1/R2 100R -> K1 hook relay -> T1 wet 600:600 -> centre-tapped hybrid -> 40 dB pad -> MIC IN
Sound card out -> 15 dB pad -> hybrid TX. Agent headset hangs off the same hybrid.
DC loop when off-hook: R1 100 + R2 100 + K1 contact + T1 primary 40-150 = 240-350 R, under the 400 R limit.
The hybrid is a Wheatstone bridge of four 620 R arms, one being the line via C, nulled by RV2 470 R.
SAFETY: T1 MUST be the wet type (20-50 mA DC without saturation). A dry voice transformer will saturate.
REGULATORY: this is not an approved interface. Use a certified DAA, or stay on the private side of a PBX.
POTS reference levels: -9 dBm (275 mV into 600 R), 300-3400 Hz, 48 V DC, ring above 150 V peak.
POTS Audio Bridge rev A · sheet 1/1 · generated from tools/xport-v92-audiobridge-model.mjs · docs/xport-nucleo-v92-audio-bridge.md

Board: 2 copper layers, 43 parts (0 on the bottom side), 29 nets, no tracks yet.

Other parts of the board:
H1, H2, H3, H4: MOUNT-M3

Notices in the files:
README.md:
its licence: the MIT grant covers code only —
> All code is copyrighted by Appditto LLC under the MIT license.
> and "server/assets" folders are copyrighted by Appditto LLC and used by
(BSD-2-Clause, © 1999–2005 Jef Poskanzer; notice retained in the file). With it
